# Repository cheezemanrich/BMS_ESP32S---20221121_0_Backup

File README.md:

# BMS_ESP32S---20221121_0_Backup

NOTE: This is an As-Is rough prototype of software and hardware.
      It is in no way ready for release and has no guarantees.
      This is open source andyou are free to do with it as you like.

Project to communicate with Valence U27-12XP battery BMS module via RS485 using an ESP32 module.

Developed with VSCode and PlatformIO

Features:
    -Uses inexpensive ESP32-DevKitC module
    -Drives color LCD module over SPI
    -Built in web server to view near real time data
    -Configured for 4 parrallel and 2 series batteries (24V)
    -Cayenne MQTT
  
Note that this project can only compile under older Espressif 3.5.0 version.

Web page files need to uploaded to SPIFFS (Terminal menu > Run task.. > PlatformIO: Upload Filesystem Image)

There is a known bug that causes reboot due to a Watchdog triggered by the Com port driver.
This is supposedly fixed in later Espressif versions but I couldn't get it to compile and don't have the time to debug it.

Some of the info used to develop this came from the DIY Solar Power Forum:
  https://diysolarforum.com/threads/interfacing-with-valence-built-in-monitoring.2183/
  https://diysolarforum.com/threads/valence-xp-super-thread.5683/

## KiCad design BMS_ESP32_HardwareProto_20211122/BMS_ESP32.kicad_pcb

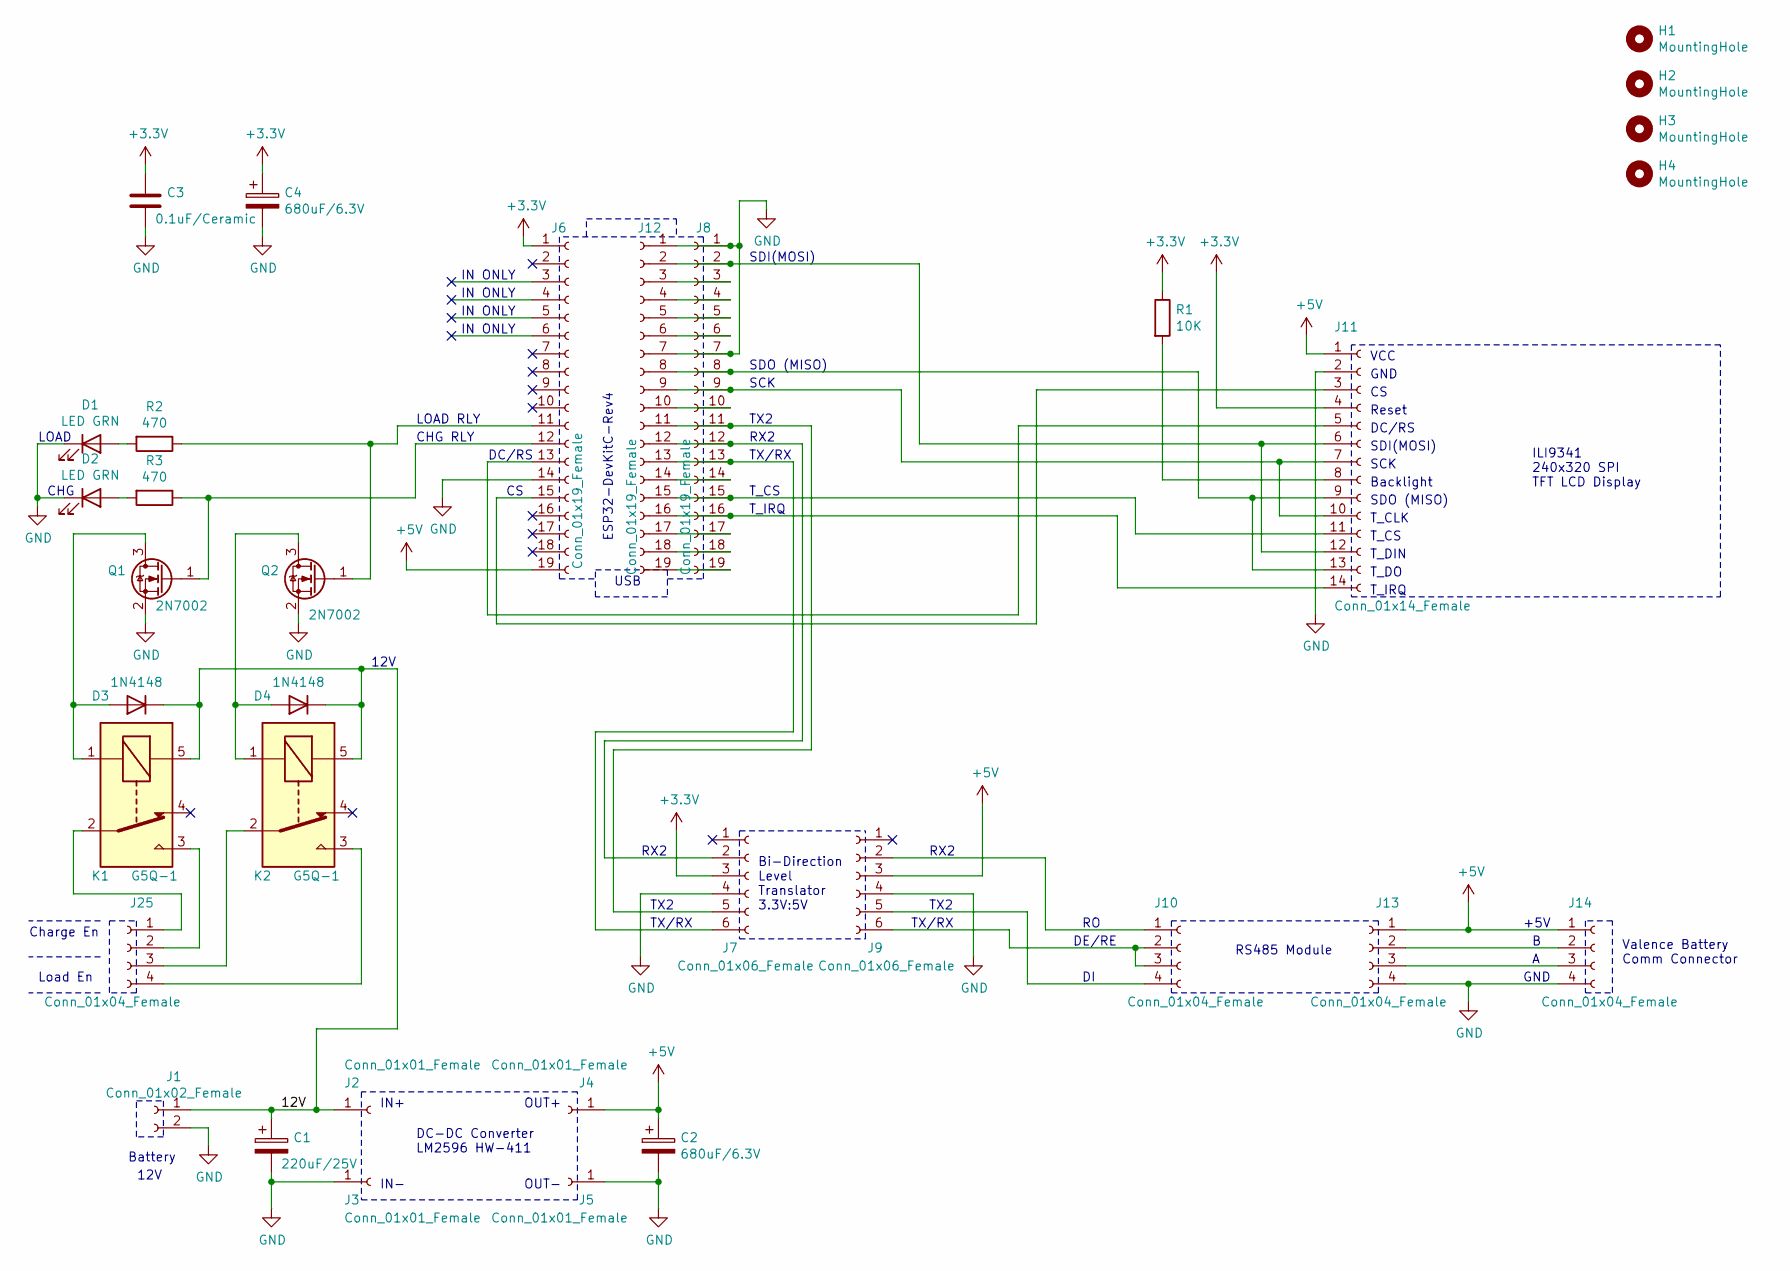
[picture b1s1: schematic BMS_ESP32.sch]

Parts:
C1: 220uF/25V; CP_Radial_D7.5mm_P2.50mm
C2, C4: 680uF/6.3V; CP_Radial_D7.5mm_P2.50mm
C3: 0.1uF/Ceramic; C_Rect_L7.0mm_W2.0mm_P5.00mm
D1, D2: LED GRN; LED_D5.0mm
D3, D4: 1N4148; D_DO-35_SOD27_P7.62mm_Horizontal
H1, H2, H3, H4: MountingHole; MountingHole_3.5mm
J1: Conn_01x02_Female; TerminalBlock_Phoenix_MKDS-1,5-2-5.08_1x02_P5.08mm_Horizont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
J2, J3, J4, J5: Conn_01x01_Female; PinSocket_1x01_P2.54mm_Vertical
J6, J8, J12: Conn_01x19_Female; PinSocket_1x19_P2.54mm_Vertical
J7, J9: Conn_01x06_Female; PinSocket_1x06_P2.54mm_Vertical
J10, J13: Conn_01x04_Female; PinSocket_1x04_P2.54mm_Vertical
J11: Conn_01x14_Female; PinSocket_1x14_P2.54mm_Vertical
J14, J25: Conn_01x04_Female; TerminalBlock_Phoenix_MKDS-1,5-4-5.08_1x04_P5.08mm_Horizont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
K1, K2: G5Q-1; Relay_SPDT_Omron-G5Q-1
Q1, Q2: 2N7002; SOT-23
R1: 10K; R_Axial_DIN0309_L9.0mm_D3.2mm_P12.70mm_Horizontal
R2, R3: 470; R_0805_2012Metric

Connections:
+3V3: C3.1, C4.1, J6.1, J7.3, J11.4, R1.1
+5V: C2.1, J4.1, J6.19, J9.3, J11.1, J13.1, J14.1
/12V: C1.1, D3.1 (K), D4.1 (K), J1.1, J2.1, K1.5, K2.5
GND: C1.2, C2.2, C3.2, C4.2, D1.1 (K), D2.1 (K), J1.2, J3.1, J5.1, J6.14, J7.4, J8.1, J8.7, J9.4, J11.2, J12.1, J12.7, J13.4, J14.4, Q1.2 (S), Q2.2 (S)
unnamed: D1.2 (A), R2.2
unnamed: D2.2 (A), R3.2
unnamed: D3.2 (A), K1.1, Q1.3 (D)
unnamed: D4.2 (A), K2.1, Q2.3 (D)
unnamed: J6.11, Q2.1 (G), R2.1
unnamed: J6.12, Q1.1 (G), R3.1
unnamed: J9.2, J10.1
unnamed: J9.6, J10.2, J10.3
unnamed: J9.5, J10.4
unnamed: J6.15, J11.3
unnamed: J6.13, J11.5
unnamed: J11.8, R1.2
unnamed: J8.9, J11.7, J11.10, J12.9
unnamed: J8.15, J11.11, J12.15
unnamed: J8.2, J11.6, J11.12, J12.2
unnamed: J8.8, J11.9, J11.13, J12.8
unnamed: J8.16, J11.14, J12.16
unnamed: J8.3, J12.3
unnamed: J8.4, J12.4
unnamed: J8.5, J12.5
unnamed: J8.6, J12.6
unnamed: J8.10, J12.10
unnamed: J7.5, J8.11, J12.11
unnamed: J7.2, J8.12, J12.12
unnamed: J7.6, J8.13, J12.13
unnamed: J8.14, J12.14
unnamed: J8.17, J12.17
unnamed: J8.18, J12.18
unnamed: J8.19, J12.19
unnamed: J13.2, J14.2
unnamed: J13.3, J14.3
unnamed: J25.1, K1.2
unnamed: J25.2, K1.3
unnamed: J25.3, K2.2
unnamed: J25.4, K2.3

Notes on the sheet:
Valence Battery Comm Connector
RS485 Module
ILI9341 240x320 SPI TFT LCD Display
DC-DC Converter LM2596 HW-411
IN+
IN-
OUT+
OUT-
Bi-Direction Level Translator 3.3V:5V
Battery
Reset
VCC
DC/RS
SDI(MOSI)
SCK
Backlight
SDO (MISO)
+5V
GND
DE/RE
RX2
TX2
TX/RX
Charge En
Load En
CHG RLY
LOAD RLY
CHG
LOAD
12V
ESP32-DevKitC-Rev4
IN ONLY
USB
T_CLK
T_CS
T_DIN
T_DO
T_IRQ

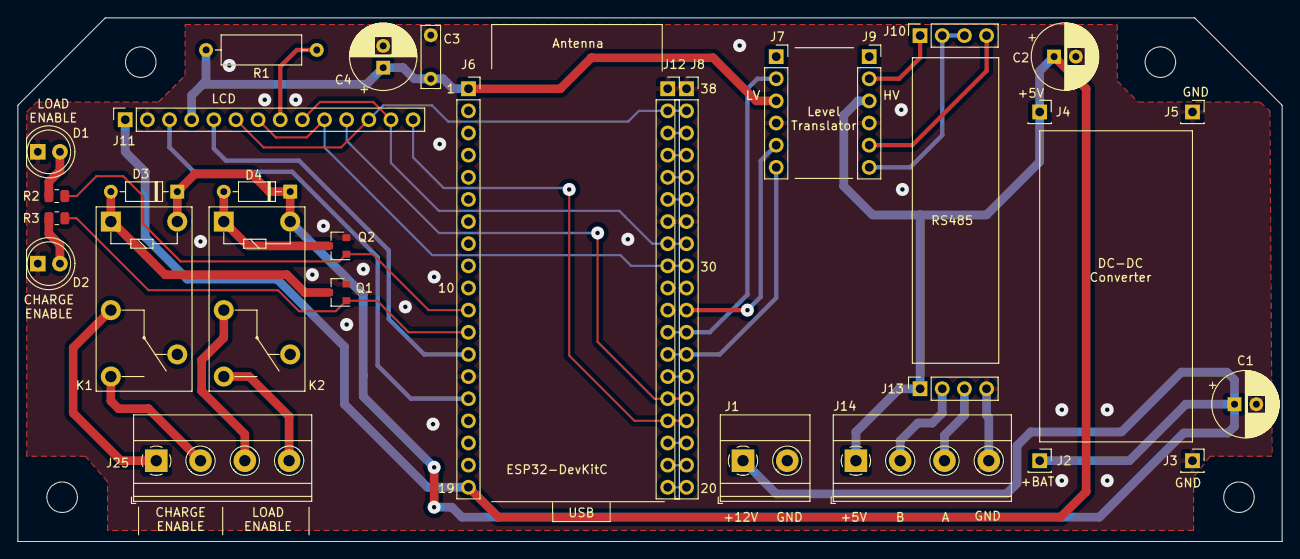
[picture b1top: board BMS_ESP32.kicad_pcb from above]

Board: 2 copper layers, 145.0 x 60.1 mm, 34 parts (0 on the bottom side), 39 nets.

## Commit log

2023-01-31 Add files via upload
    Add hardware prototype KiCAD files.
